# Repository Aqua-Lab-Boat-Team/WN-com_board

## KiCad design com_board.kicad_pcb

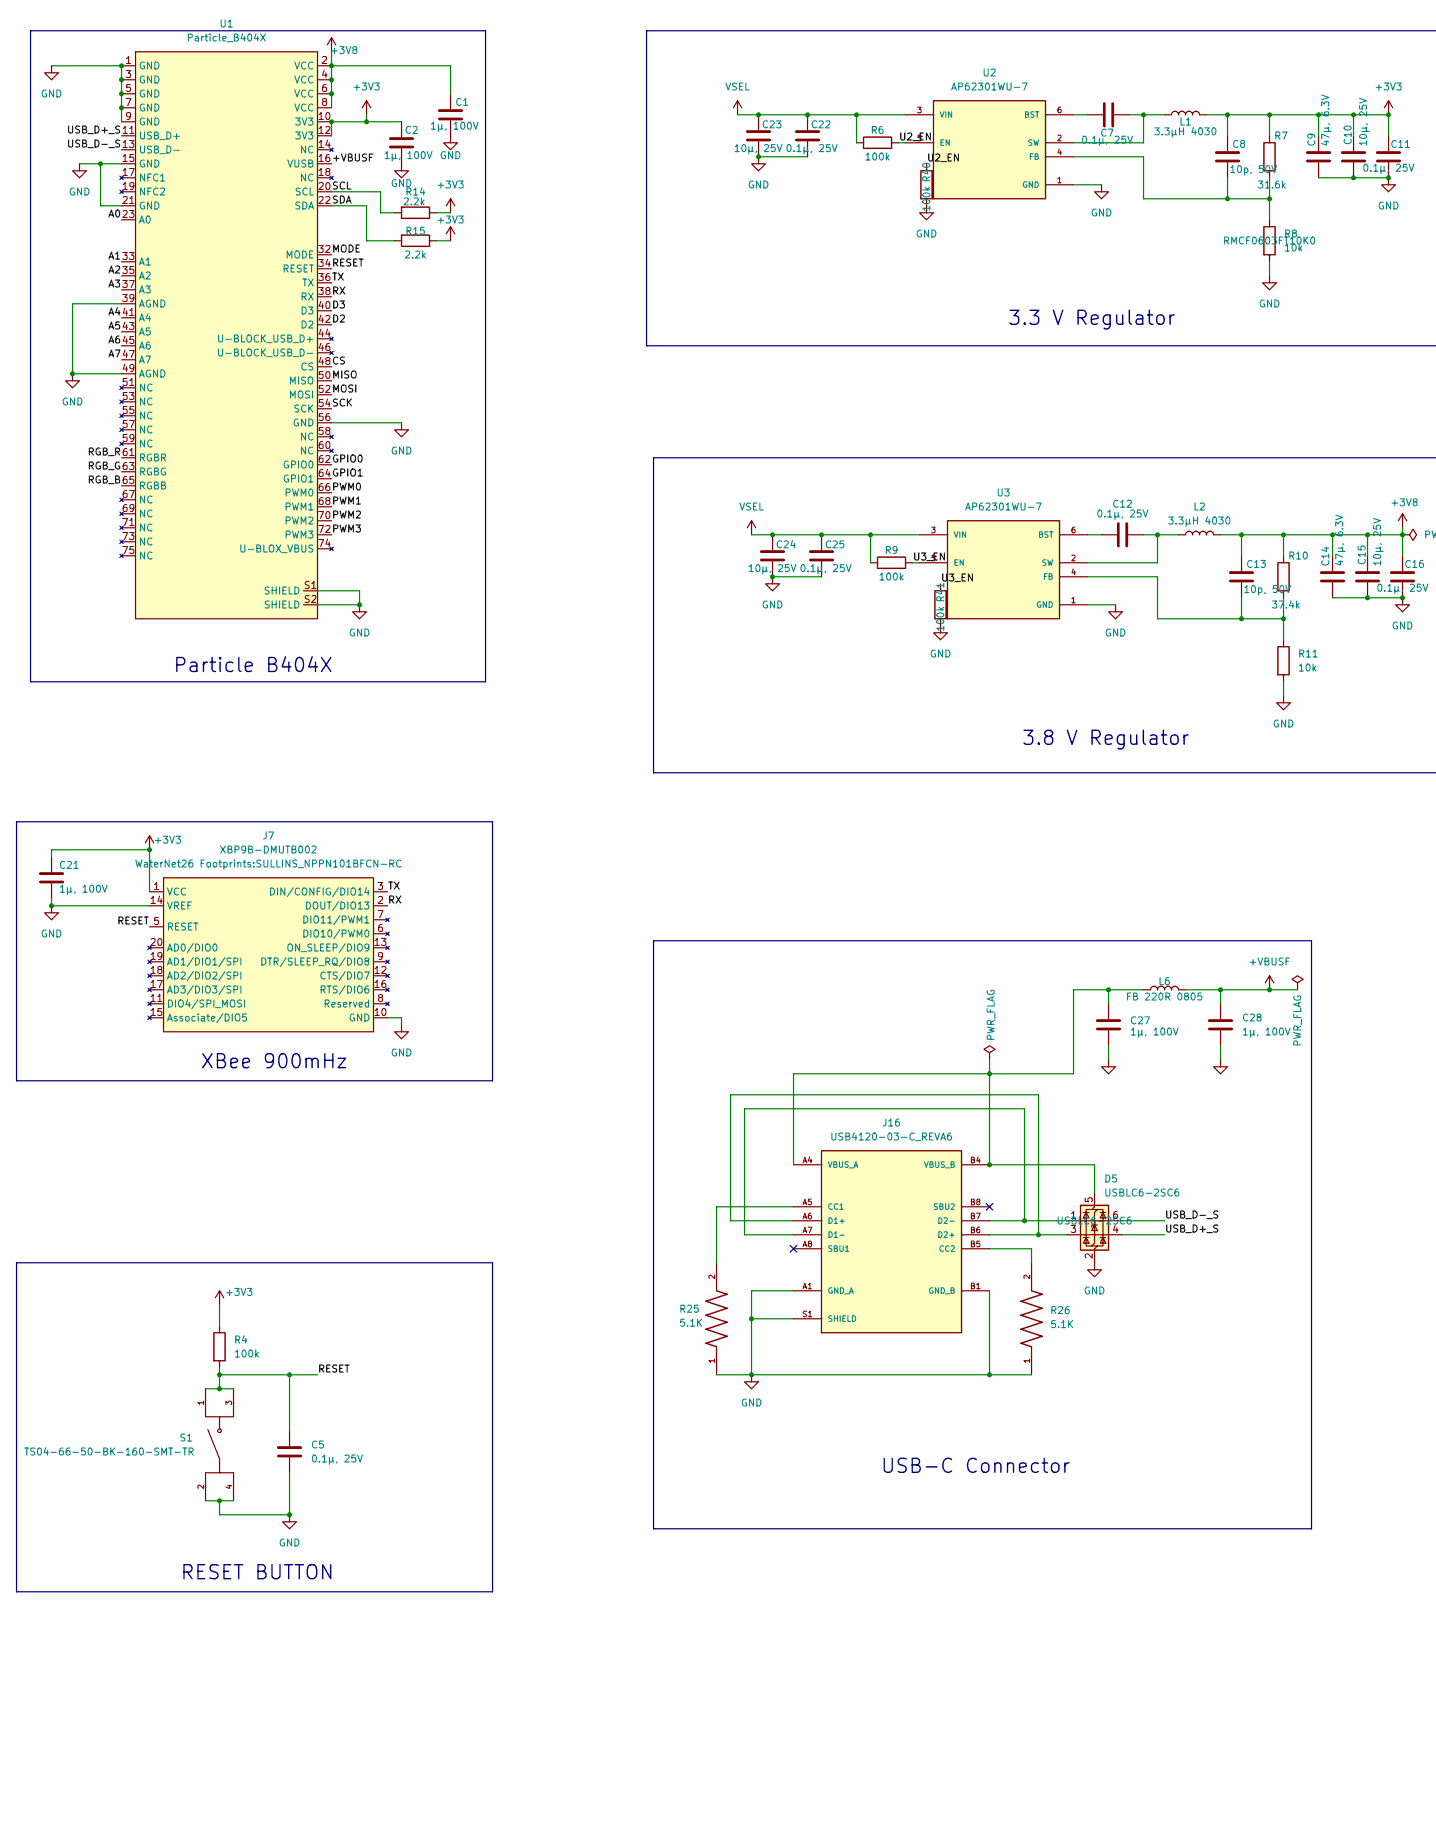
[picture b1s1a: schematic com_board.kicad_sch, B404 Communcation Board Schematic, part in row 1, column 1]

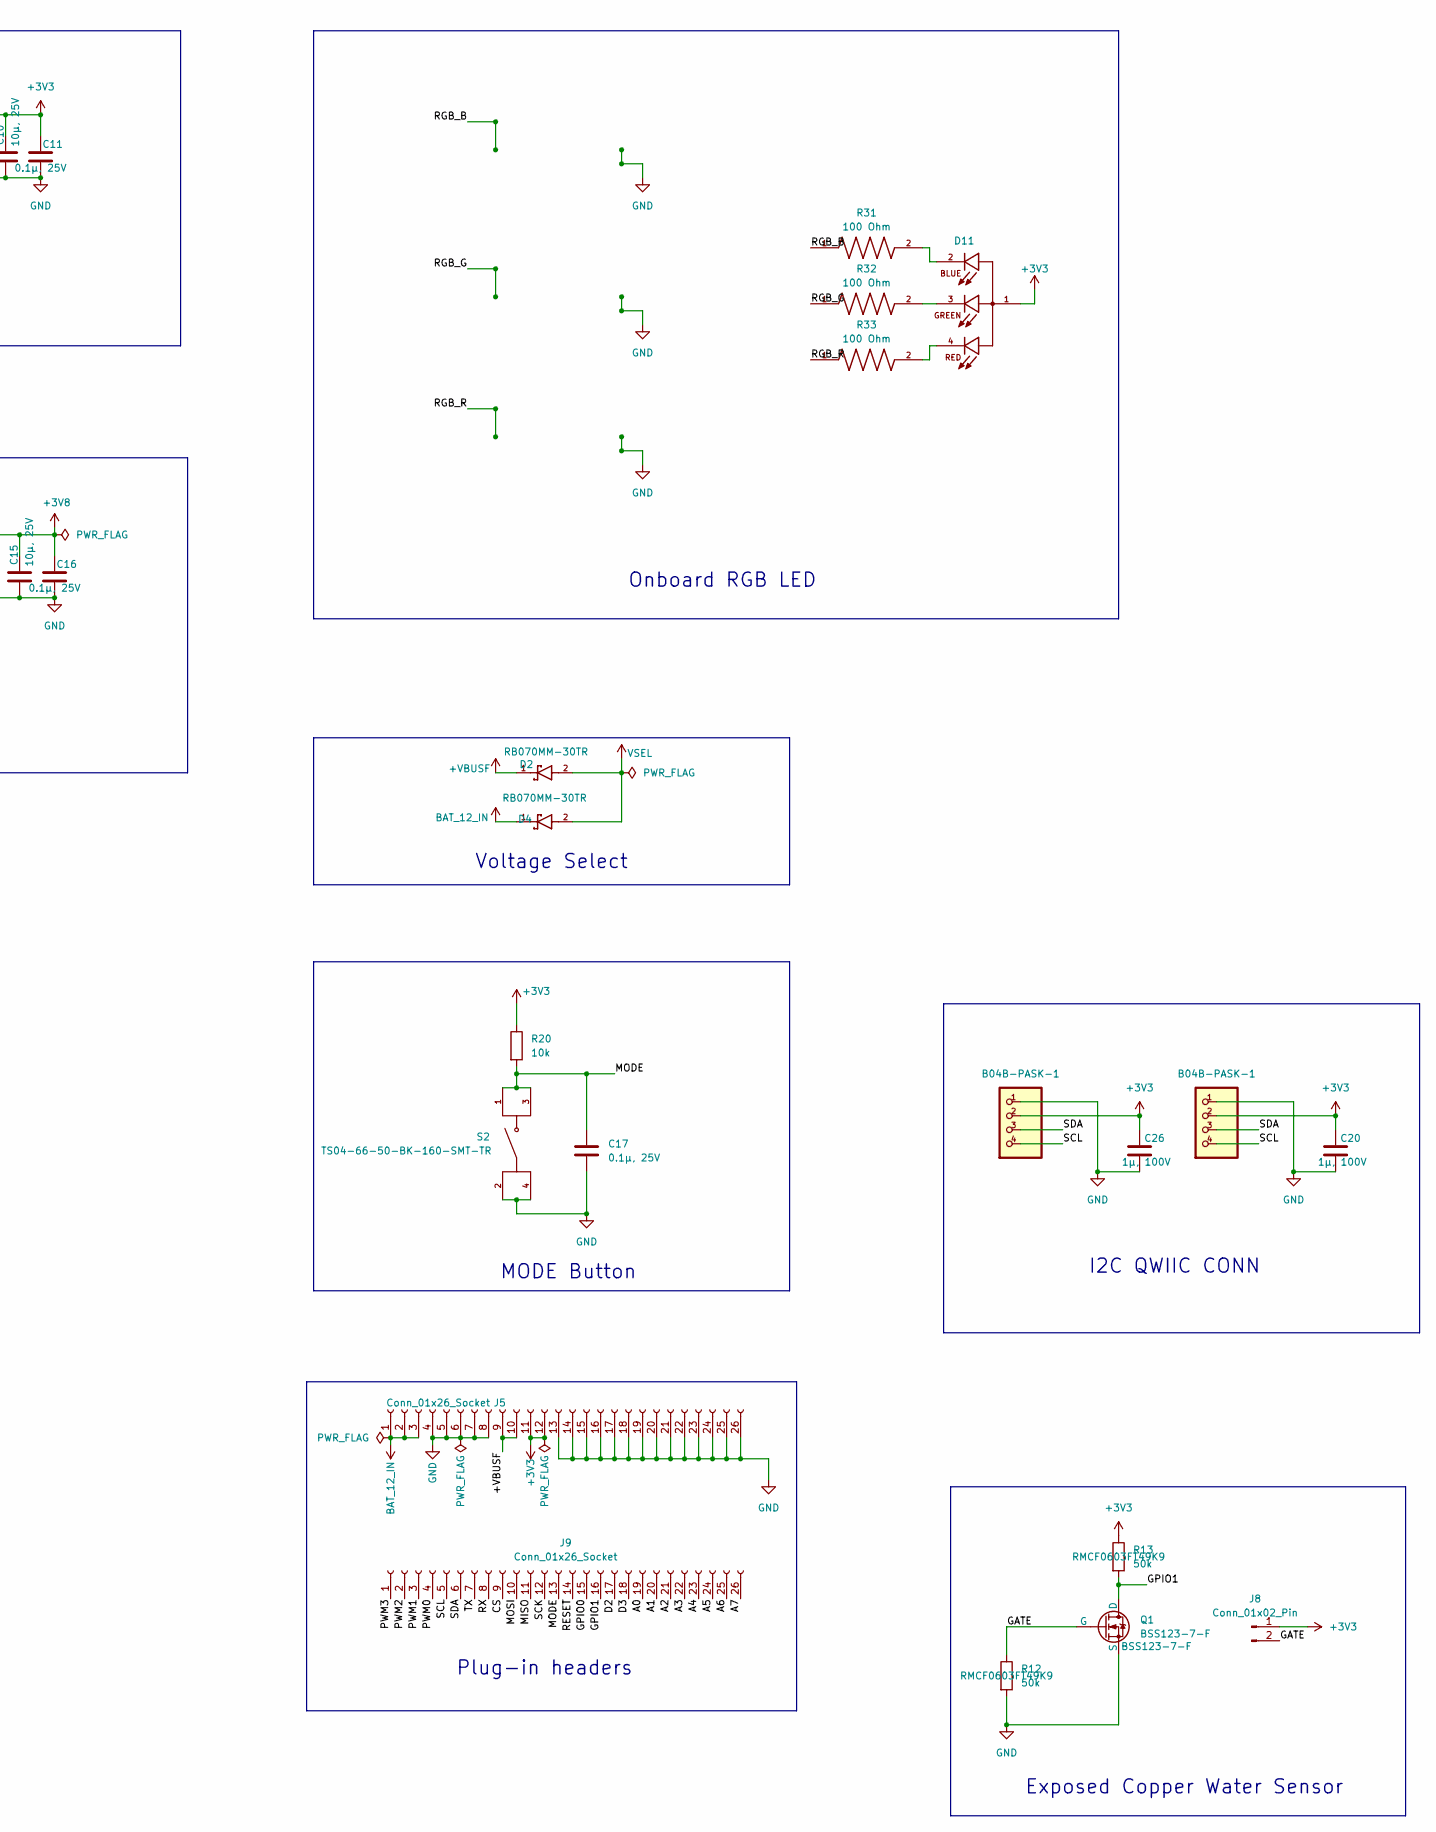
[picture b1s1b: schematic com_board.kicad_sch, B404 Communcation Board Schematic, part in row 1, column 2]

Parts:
C1, C2, C20, C21, C26, C27, C28: 1µ, 100V; CAPC2012X145N
C5, C7, C11, C12, C16, C17, C22, C25: 0.1µ, 25V; CAPC2012X95N
C8, C13: 10p, 50V; CAPC2012X95N
C9, C14: 47µ, 6.3V; CAPC3216X180N
C10, C15, C23, C24: 10µ, 25V; CAPC2012X145N
D2, D4: RB070MM-30TR; DIO_RB070MM-30TR
D5: USBLC6-2SC6; SOT-23-6
D11: CLMVC-FKA-CL1D1L71BB7C3C3; LED_CLMVC-FKA-CL1D1L71BB7C3C3; PARTREV 14
J5, J9: Conn_01x26_Socket; PinHeader_1x26_P2.54mm_Vertical
J7: XBP9B-DMUTB002; SULLINS_NPPN101BFCN-RC
J8: Conn_01x02_Pin; PinHeader_1x02_P2.54mm_Vertical
J16: USB4120-03-C_REVA6; GCT_USB4120-03-C_REVA6; PARTREV A6
JP2, JP3: B04B-PASK-1
L1, L2: 3.3µH 4030; L_Wuerth_MAPI-4030
L6: FB 220R 0805; L_0805_2012Metric
Q1: BSS123-7-F; SOT95P240X110-3N
R4, R6, R9, R40, R41: 100k; RES_ERA6AEB104V
R7: 31.6k; RES_ERA6AEB3162V
R8, R11, R20: 10k; RES_ERA6AEB103V
R10: 37.4k; RESC1608X55N
R12, R13: 50k; RESC1608X55N
R14, R15: 2.2k; RESC1608X55N
R25, R26: 5.1K; RESC1508X55N
R31, R32, R33: 100 Ohm; RES_ERJ3EKF1000V; PARTREV 3/1/2020
S1, S2: TS04-66-50-BK-160-SMT-TR; SW_TS04-66-50-BK-160-SMT-TR; PARTREV 1.04mm
U1: Particle_B404X; b404x
U2, U3: AP62301WU-7; SOT95P280X100-6N; PARTREV Rev. 3 - 2

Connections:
+3V3: C2.1, C8.1, C9.1, C10.1, C11.1, C20.1, C21.1, C26.1, D11.1, J5.11, J5.12, J7.1 (VCC_1), J8.1, JP2.2, JP3.2, L1.2, R4.1, R7.1, R13.1, R14.1, R15.1, R20.1, U1.10 (3V3), U1.12 (3V3)
+3V8: C1.1, C13.1, C14.1, C15.1, C16.1, L2.2, R10.1, U1.2 (VCC), U1.4 (VCC), U1.6 (VCC), U1.8 (VCC)
+VBUSF: C28.1, D2.1, J5.9, J5.10, L6.2, U1.16 (VUSB)
/A0: J9.19, U1.23 (A0)
/A1: J9.20, U1.33 (A1)
/A2: J9.21, U1.35 (A2)
/A3: J9.22, U1.37 (A3)
/A4: J9.23, U1.41 (A4)
/A5: J9.24, U1.43 (A5)
/A6: J9.25, U1.45 (A6)
/A7: J9.26, U1.47 (A7)
/CS: J9.9, U1.48 (CS)
/D2: J9.17, U1.42 (D2)
/D3: J9.18, U1.40 (D3)
/GATE: J8.2, Q1.1 (D), R12.1
/GPIO0: J9.15, U1.62 (GPIO0)
/GPIO1: J9.16, Q1.3 (S), R13.2, U1.64 (GPIO1)
/MISO: J9.11, U1.50 (MISO)
/MODE: C17.1, J9.13, R20.2, S2.1, S2.3, U1.32 (MODE)
/MOSI: J9.10, U1.52 (MOSI)
/PWM0: J9.4, U1.66 (PWM0)
/PWM1: J9.3, U1.68 (PWM1)
/PWM2: J9.2, U1.70 (PWM2)
/PWM3: J9.1, U1.72 (PWM3)
/RESET: C5.1, J7.5 (RESET_5), J9.14, R4.2, S1.1, S1.3, U1.34 (RESET)
/RGB_B: R31.1, U1.65 (RGBB)
/RGB_G: R32.1, U1.63 (RGBG)
/RGB_R: R33.1, U1.61 (RGBR)
/RX: J7.2 (DOUT/DIO13_2), J9.8, U1.38 (RX)
/SCK: J9.12, U1.54 (SCK)
/SCL: J9.5, JP2.4, JP3.4, R14.2, U1.20 (SCL)
/SDA: J9.6, JP2.3, JP3.3, R15.2, U1.22 (SDA)
/TX: J7.3 (DIN/CONFIG/DIO14_3), J9.7, U1.36 (TX)
/U2_EN: R6.2, R40.1, U2.5 (EN)
/U3_EN: R9.2, R41.1, U3.5 (EN)
/USB_D+_S: D5.4 (I/O2), U1.11 (USB_D+)
/USB_D-_S: D5.6 (I/O1), U1.13 (USB_D-)
BAT_12_IN: D4.1, J5.1, J5.2, J5.3
GND: C1.2, C2.2, C5.2, C9.2, C10.2, C11.2, C14.2, C15.2, C16.2, C17.2, C20.2, C21.2, C22.2, C23.2, C24.2, C25.2, C26.2, C27.2, C28.2, D5.2 (GND), J5.4, J5.5, J5.6, J5.7, J5.8, J5.13, J5.14, J5.15, J5.16, J5.17, J5.18, J5.19, J5.20, J5.21, J5.22, J5.23, J5.24, J5.25, J5.26, J7.10 (GND_10), J7.14 (AD3/DIO3/SPI_17), J16.A1 (GND_A), J16.A12 (GND_A), J16.B1 (GND_B), J16.B12 (GND_B), J16.S1 (SHIELD), J16.S2 (SHIELD), J16.S3 (SHIELD), J16.S4 (SHIELD), JP2.1, JP3.1, Q1.2 (G), R8.2, R11.2, R12.2, R25.1, R26.1, R40.2, R41.2, S1.2, S1.4, S2.2, S2.4, U1.1 (GND), U1.3 (GND), U1.5 (GND), U1.7 (GND), U1.9 (GND), U1.15 (GND), U1.21 (GND), U1.39 (AGND), U1.49 (AGND), U1.56 (GND), U1.S1 (SHIELD), U1.S2 (SHIELD), U2.1 (GND), U3.1 (GND); also elsewhere on the board
unnamed: D11.2, R31.2
unnamed: D11.3, R32.2
unnamed: D11.4, R33.2
unnamed: J16.A5 (CC1), R25.2
unnamed: J16.B5 (CC2), R26.2
unnamed: D5.3 (I/O2), J16.A6 (D1+), J16.B6 (D2+)
unnamed: D5.1 (I/O1), J16.A7 (D1-), J16.B7 (D2-)
unnamed: C7.1, U2.6 (BST)
unnamed: C8.2, R7.2, R8.1, U2.4 (FB)
unnamed: C7.2, L1.1, U2.2 (SW)
unnamed: C12.1, U3.6 (BST)
unnamed: C13.2, R10.2, R11.1, U3.4 (FB)
unnamed: C12.2, L2.1, U3.2 (SW)
VBUS_A: C27.1, D5.5 (VBUS), J16.A4 (VBUS_A), J16.A9 (VBUS_A), J16.B4 (VBUS_B), J16.B9 (VBUS_B), L6.1
VSEL: C22.1, C23.1, C24.1, C25.1, D2.2, D4.2, R6.1, R9.1, U2.3 (VIN), U3.3 (VIN)

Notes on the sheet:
Voltage Select
Particle B404X
Plug-in headers
XBee 900mHz
Exposed Copper Water Sensor
RESET BUTTON
3.3 V Regulator
3.8 V Regulator
Onboard RGB LED
MODE Button
USB-C Connector
I2C QWIIC CONN

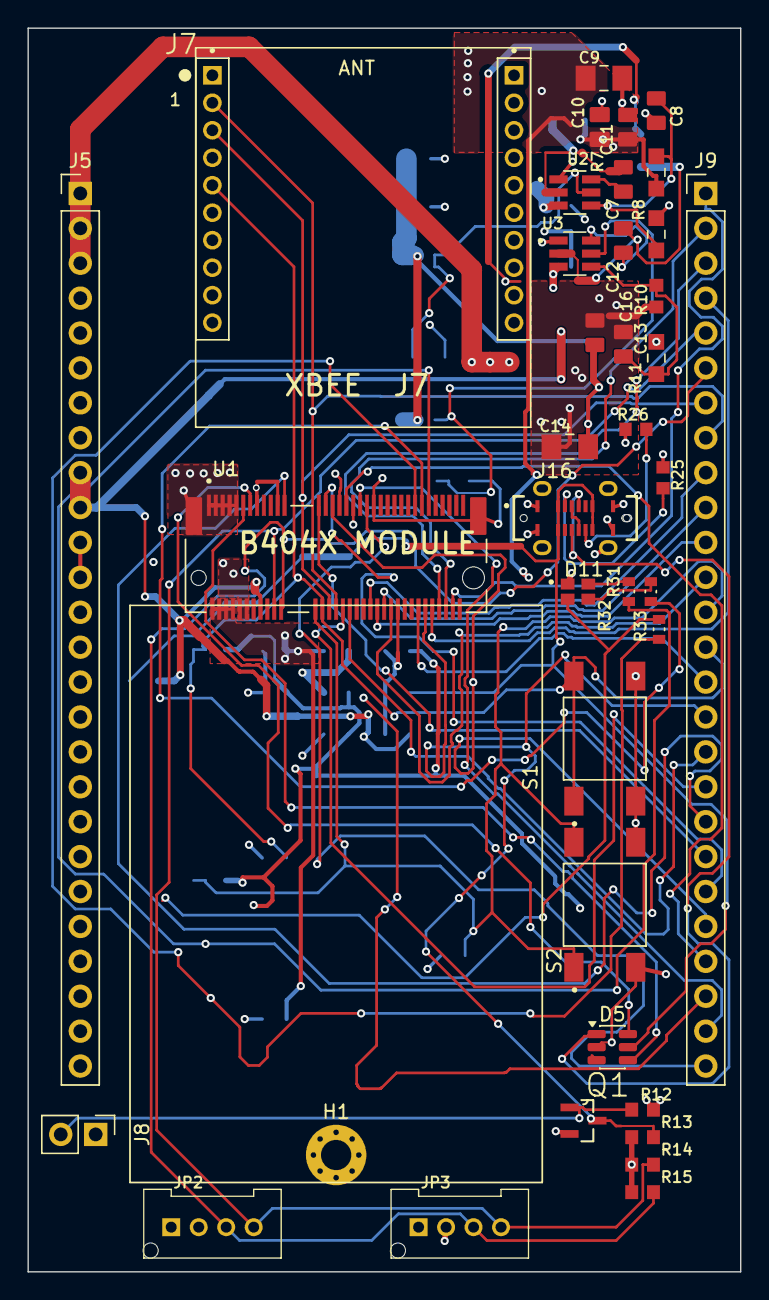
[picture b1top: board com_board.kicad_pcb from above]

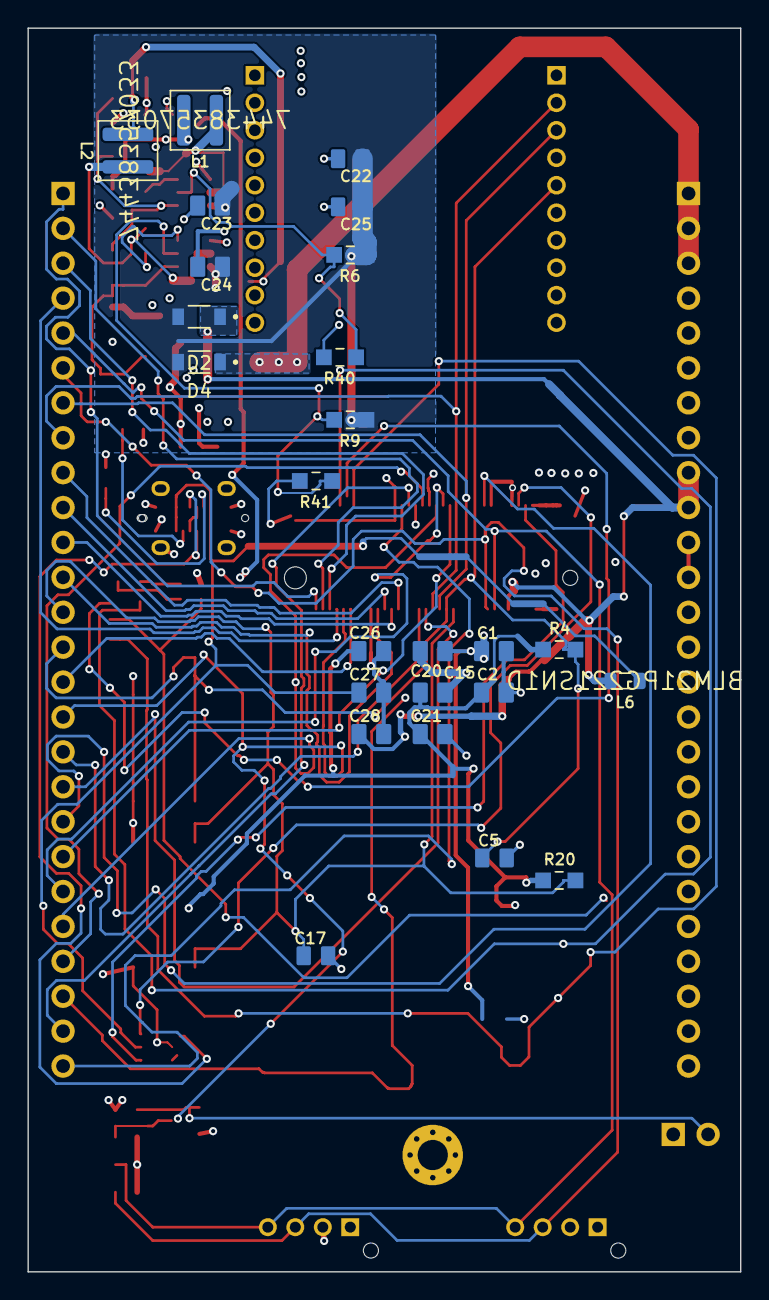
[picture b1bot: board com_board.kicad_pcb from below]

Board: 4 copper layers, 51.8 x 90.5 mm, 63 parts (25 on the bottom side), 54 nets.

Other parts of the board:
H1: M2 standoff (JAE SM3ZS067U410-NUT1-R1200); MountingHole_2.2mm_M2_Pad_Via

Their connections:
GND: H1.1; also elsewhere on the board

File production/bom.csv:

Designator,Footprint,Quantity,Value,LCSC Part #
"C1, C2, C20, C21, C26, C27, C28",CAPC2012X145N,7,"1µ, 100V",
"C10, C13, C15, C23, C24, C8",CAPC2012X145N,6,"10µ, 25V",
"C11, C12, C16, C17, C22, C25, C5, C7",CAPC2012X95N,8,"0.1µ, 25V",
"C14, C9",CAPC3216X180N,2,"47µ, 6.3V",
"C68, C69, C76",CAPC2012X95N,3,0.1uF 25V,
D11,LED_CLMVC-FKA-CL1D1L71BB7C3C3,1,CLMVC-FKA-CL1D1L71BB7C3C3,
"D2, D4",DIO_RB070MM-30TR,2,RB070MM-30TR,
D5,SOT-23-6,1,USBLC6-2SC6,
J16,GCT_USB4120-03-C_REVA6,1,USB4120-03-C_REVA6,
"J5, J9",PinHeader_1x26_P2.54mm_Vertical,2,Conn_01x26_Socket,
J7,SULLINS_NPPN101BFCN-RC,1,XBP9B-DMUTB002,
J8,PinHeader_1x02_P2.54mm_Vertical,1,Conn_01x02_Pin,
"JP2, JP3",B04B-PASK-1,2,B04B-PASK-1,
"L1, L2, L6",INDC1608X95N,3,3.3µ,
Q1,SOT95P240X110-3N,1,NMOS,
R10,RESC1608X55N,1,37.4k,
"R11, R66, R67, R68, R8",RES_ERA6AEB103V,5,10k,
"R12, R13",RESC1608X55N,2,50k,
"R14, R15",RESC1608X55N,2,2.2k,
"R20, R4, R6, R9",RES_ERA6AEB104V,4,100k,
"R25, R26",RESC1508X55N,2,5.1K,
"R31, R32, R33",RES_ERJ3EKF1000V,3,100 Ohm,
R7,RES_ERA6AEB3162V,1,31.6k,
"S1, S2",SW_TS04-66-50-BK-160-SMT-TR,2,TS04-66-50-BK-160-SMT-TR,
U1,b404x,1,Particle_B404X,
"U16, U17, U18",SOT95P240X110-3N,3,BSS123-7-F,BSS123-7-F
"U2, U3",SOT95P280X100-6N,2,AP62301WU-7,
